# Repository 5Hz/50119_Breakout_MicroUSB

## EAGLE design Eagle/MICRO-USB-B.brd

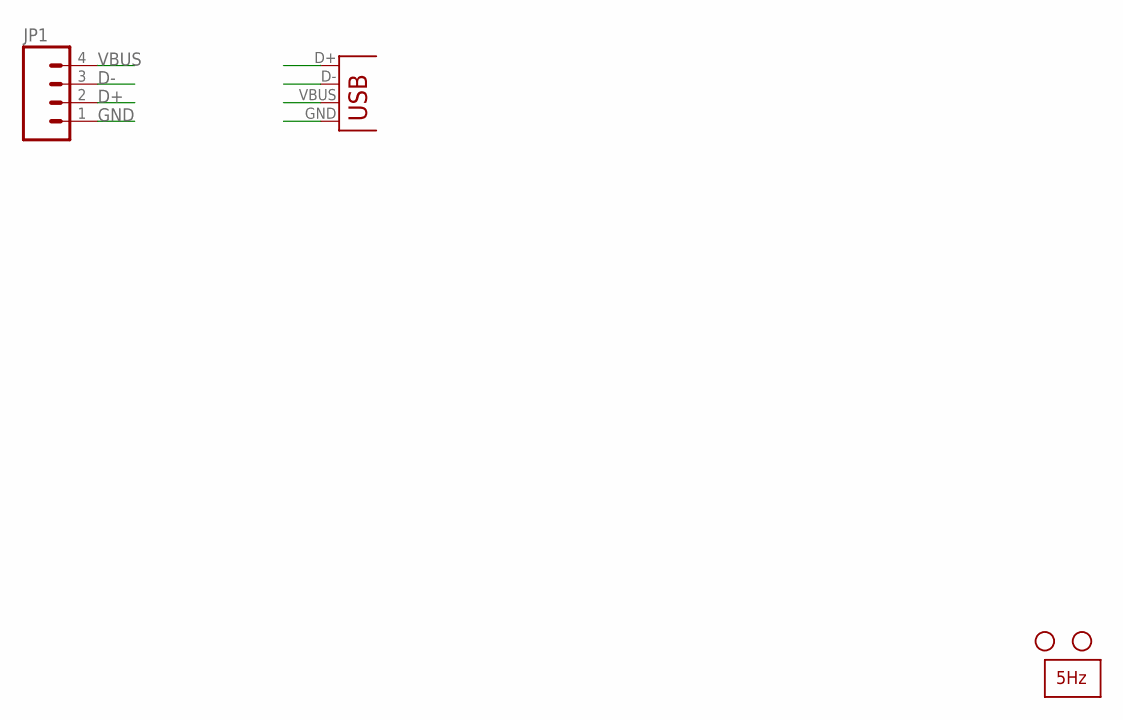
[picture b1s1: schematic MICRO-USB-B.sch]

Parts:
JP1: M04PTH; 1X04
JP3, JP4: STAND-OFF
U$1: LOGO2_SILKC5MM; CIRCULO2_5MM
X1: USB-MICROB

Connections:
D+: JP1.2, X1.D+
D-: JP1.3, X1.D-
GND: JP1.1, X1.GND
VBUS: JP1.4, X1.VBUS

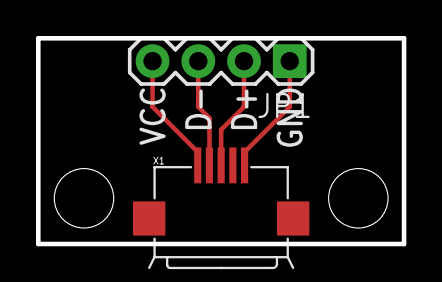
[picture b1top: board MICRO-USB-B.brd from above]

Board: 2 copper layers, 20.3 x 11.4 mm, 5 parts (1 on the bottom side), 4 nets.

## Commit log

2014-01-14 creación
